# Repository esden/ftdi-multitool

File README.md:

This repository contains hardware designs for an FTDI FT232H based multi purpose tool.

The design goal is to make a very small FTDI breakout board that has a defined connector. That defined connector can receive a wide range of easy to design adapters. The adapters can then plug in into any variety of targets. The FTDI chip has a fairly wide range of protocols it supports, making it ideal for many applications.

## Protocol List
* TTY UART Serial (with or without hardware flow control)
* SPI using MPSSEngine
* I2C
* JTAG
* CPU Data Address

## Datasheet
For more information on the FTDI FT232 please refer to the chip's [datasheet](http://www.ftdichip.com/Support/Documents/DataSheets/ICs/DS_FT232H.pdf).

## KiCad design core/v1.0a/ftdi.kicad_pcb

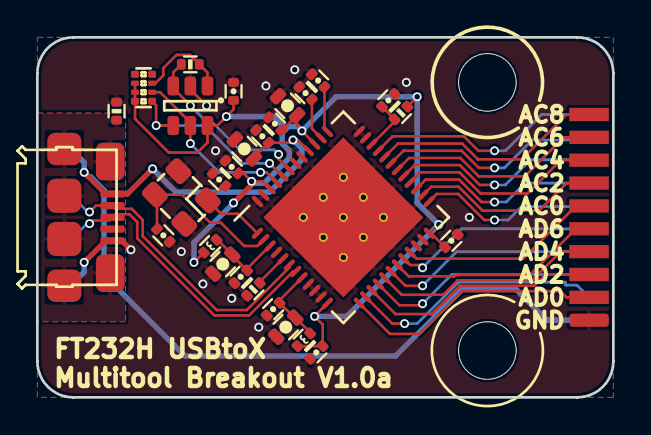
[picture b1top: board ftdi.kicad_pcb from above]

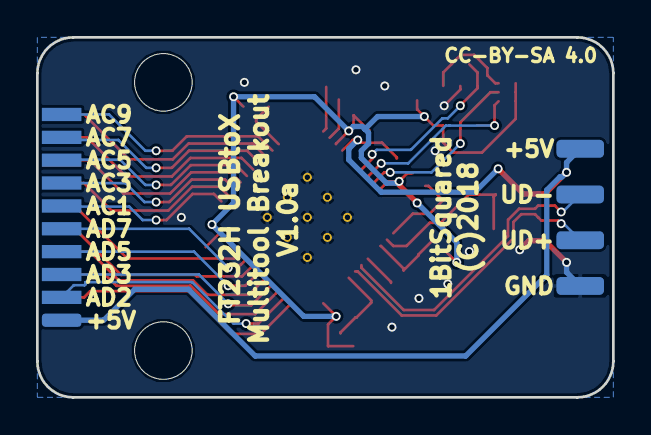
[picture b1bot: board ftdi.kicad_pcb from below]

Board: 2 copper layers, 32.0 x 20.0 mm, 33 parts (4 on the bottom side), 35 nets.

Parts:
C1, C8, C10, C12, C13, C14, C16, C18, C19, C20: 100n; C_0402
C2, C3: 10p; C_0402
C4: 10n; C_0402
C5, C6, C7, C9: 4u7; C_0603
J1: Conn; FTSH-EDGE-20pin
L1, L2: 600; L_0402
P1: pkl_USB_OTG; Connector_USB_Micro_B_SMD
P2, P3, P4, P5: UP; PAD_SMD_1x2.65
R1: 1M; R_0402
R2: 10k; R_Array_Convex_4x0402
R6: 2k2; R_0402
R8: 12k; R_0402
R9: 10k; R_0402
U1: 93C46B-SOT-23-6; SOT-23-6
U2: FT232H; QFN-48-1EP_8x8mm_Pitch0.5mm
X1: 12MHz; ABM8

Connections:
+3V3: C1.1, C5.1, C8.1, C18.1, C19.1, C20.1, L1.1, L2.1, R2.2, R2.4, R2.6, R9.2, U1.6, U2.12, U2.24, U2.39, U2.46
+5V: C7.1, C10.1, J1.2, P1.1, P2.1, U2.40
/ACBUS0: J1.11, U2.21
/ACBUS1: J1.12, U2.25
/ACBUS2: J1.13, U2.26
/ACBUS3: J1.14, U2.27
/ACBUS4: J1.15, U2.28
/ACBUS5: J1.16, U2.29
/ACBUS6: J1.17, U2.30
/ACBUS7: J1.18, U2.31
/ACBUS8: J1.19, U2.32
/ACBUS9: J1.20, U2.33
/ADBUS0: J1.3, U2.13
/ADBUS1: J1.4, U2.14
/ADBUS2: J1.5, U2.15
/ADBUS4: J1.7, U2.17
/ADBUS5: J1.8, U2.18
/ADBUS6: J1.9, U2.19
/ADBUS7: J1.10, U2.20
/USB_D+: P1.3, P4.1, U2.7
/USB_D-: P1.2, P3.1, U2.6
/VCCA: C16.1, U2.37
/VCORE: C14.1, U2.38
/shield: P1.GND, R1.2
GND: C1.2, C2.2, C3.2, C4.2, C5.2, C6.2, C7.2, C8.2, C9.2, C10.2, C12.2, C13.2, C14.2, C16.2, C18.2, C19.2, C20.2, J1.1, P1.5, P5.1, R1.1, R8.1, U1.2, U2.4, U2.9, U2.10, U2.11, U2.22, U2.23, U2.35, U2.36, U2.41, U2.42, U2.47, U2.48, U2.49, X1.GND
unnamed: C2.1, U2.1, X1.1
unnamed: C3.1, U2.2, X1.2
unnamed: C4.1, R9.1, U2.34
unnamed: C6.1, C12.1, L2.2, U2.3
unnamed: C9.1, C13.1, L1.2, U2.8
unnamed: R2.1, U1.4, U2.44
unnamed: R2.3, U1.5, U2.45
unnamed: R2.5, R6.2, U1.1
unnamed: R6.1, U1.3, U2.43
unnamed: R8.2, U2.5

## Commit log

2018-05-09 Initial commit.
2018-05-09 Corrected pmod UART pinout and added INT/RST pins.
2018-05-09 Added FTDI JTAG adapter.
2018-05-09 Fixed PMOD pinout on SPI adapter.
2018-05-09 Corrected the symbol table list.
2018-05-09 Corrected fill on the UART PMOD adapter.
2018-05-09 Improved legend of the FT232 USBtoX Multitool Breakout.
2018-05-09 Updated PKL.
2018-05-09 Initial commit of the ftdi 100mil adapter.
2018-05-09 Corrected parameters for gerber export.
2018-05-09 Added FTDI PMOD FIFO adapter.
2018-05-09 Changed the ftdi breakout design to use a 50mil header.
    This also decreases the width of the breakout, which will allow us to
    make standard complient 0.8" wide PMOD modules using the breakout board
    as a basis.
2018-05-09 A bunch of minor fixes.
    * PWRSAV instead of WRSAV in signal table.
    * 0.05 solder stop opening instead of 0.2
    * Better copper fill parameters.
2018-05-09 Added ftdi bitsy programmer adapter.
2018-05-09 Bumped the ftdi adapter to V1.0a. + minor improvements.
2018-05-09 Added FTDI UART PMOD adapter.
2018-05-09 Updated the SPI PMOD adapter to a full PMOD interface.
    This setup allows the use of the adapter with INT and RST lines too.
2018-05-09 Initial commit of the FTDI FT232 breakout.
    This breakout board is meant to be used as a multipurpose tool to work
    and interface with the icebreaker fpga boards and more.
2018-05-09 Added ftdi spi pmod adapter.
2018-05-09 Added dimension drawing.
2018-05-09 Removed paste from the edge connector pads.
2018-05-09 Placement plan adjustments.
2018-05-09 Some preliminary basic readme data.
2018-05-09 Added some 3d models.

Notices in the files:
core/v1.0a/ftdi.kicad_pcb:
(C) 2018 Piotr Esden-Tempski
(C) 2018 1BitSquared
License: CC-BY-SA 4.0
CC-BY-SA 4.0
(C)2018
